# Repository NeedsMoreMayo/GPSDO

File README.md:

# GPSDO
A GPSDO built around readily available hardware

## Current Status
The GPSDO is a work in progress (Jan 2024). It's the first time I'm working with the AVR-Dx family, and it's looking very promissing.
	
## The GPSDO working principle
I've pulled together a number of designs, and ignored a lot of forum comments. The design uses a NEO-M8N GPS as PPS source, the generated pulse is configurable contrary to some sources. The OCXO is a cheap one. I'm using the Time Integration method (TIC) to tune the crystal. The main source of inspiration is the 2011 design by Kasper Kjeld Pedersen (https://n1.taur.dk/gpsdo2a.pdf).

The OCXO clock is fed to the uC as external clock. This way the control runs synchronous to the XO and we need to measure 2 events to keep the OCXO in check:
- the number of pulses contained within 1 sec of PPS. We can count this with the TCD or TCB counter.
- the fraction of the XO pulse that runs out of phase with the PPS. In other words, the out-of-phaseness of the PPS with the rest of the system. We measure this with a TIC (Time Interpolation Counter)

The corrections are fed to a 18-bit DAC which corrects the voltage control of the OCXO. The phase of the XO isn't adjusted, and doesn't need to be. The 1 PPS envelope contains exactly 10M clocks, and the uC is always synced to the clock.

### TIC

### Output stage
The output driver and clock dividers were copied from Bertrand Zauhar's GPSDO design (https://ve2zaz.net/GPS_Std/Downloads/VE2ZAZ_GPS_Derived_Std_QEX_09_10_2006.pdf). The RS422 line driver is changed to DS34C87T because of rise time/propagation delay considerations. Coupling capacitors are High-Voltage devices.

## Parts
- GPS module: GY-GPSV3 NEO-M8N GPS Module from aliexpress.
- OCXO: OC5SC25
- uC: AVR32DB28
- Output line driver: DS34C87T
- LDO: 2 x AZ1117, one for OCXO and one for digital
- DAC: AD5680

## The AVR-DB uC
I originally planned on building it with an atmega. Then changed my mind to an STM32 with ChibiOS. Now I've chosen AVR32DB28. I hope to become familiar enough with it to help porting ChibiOS to the AVR-DX family.

### Compilation
Just type make, the makefile is a template from WinAVR I adapted.
If your avr-gcc doesn't support this device, you probably need to add the support pack from MicroChip's site:
1. goto http://packs.download.atmel.com/
2. download the Atmel AVR-Dx Series Device Support. It's an archive. Uncompress it in ./xyz/
3. copy ./xyz/gcc/dev/avr32db28/avrxmega3/crtavr32db28.o and libavr32db28.a to /yourGCCAVRpath/avr/lib/avrxmega3/
4. copy ./xyz/gcc/dev/avr32db28/device-specs/specs-avr32db28 to /yourGCCAVRpath/avr/lib/avr-gcc/version/gcc/avr/subversion/device-specs/

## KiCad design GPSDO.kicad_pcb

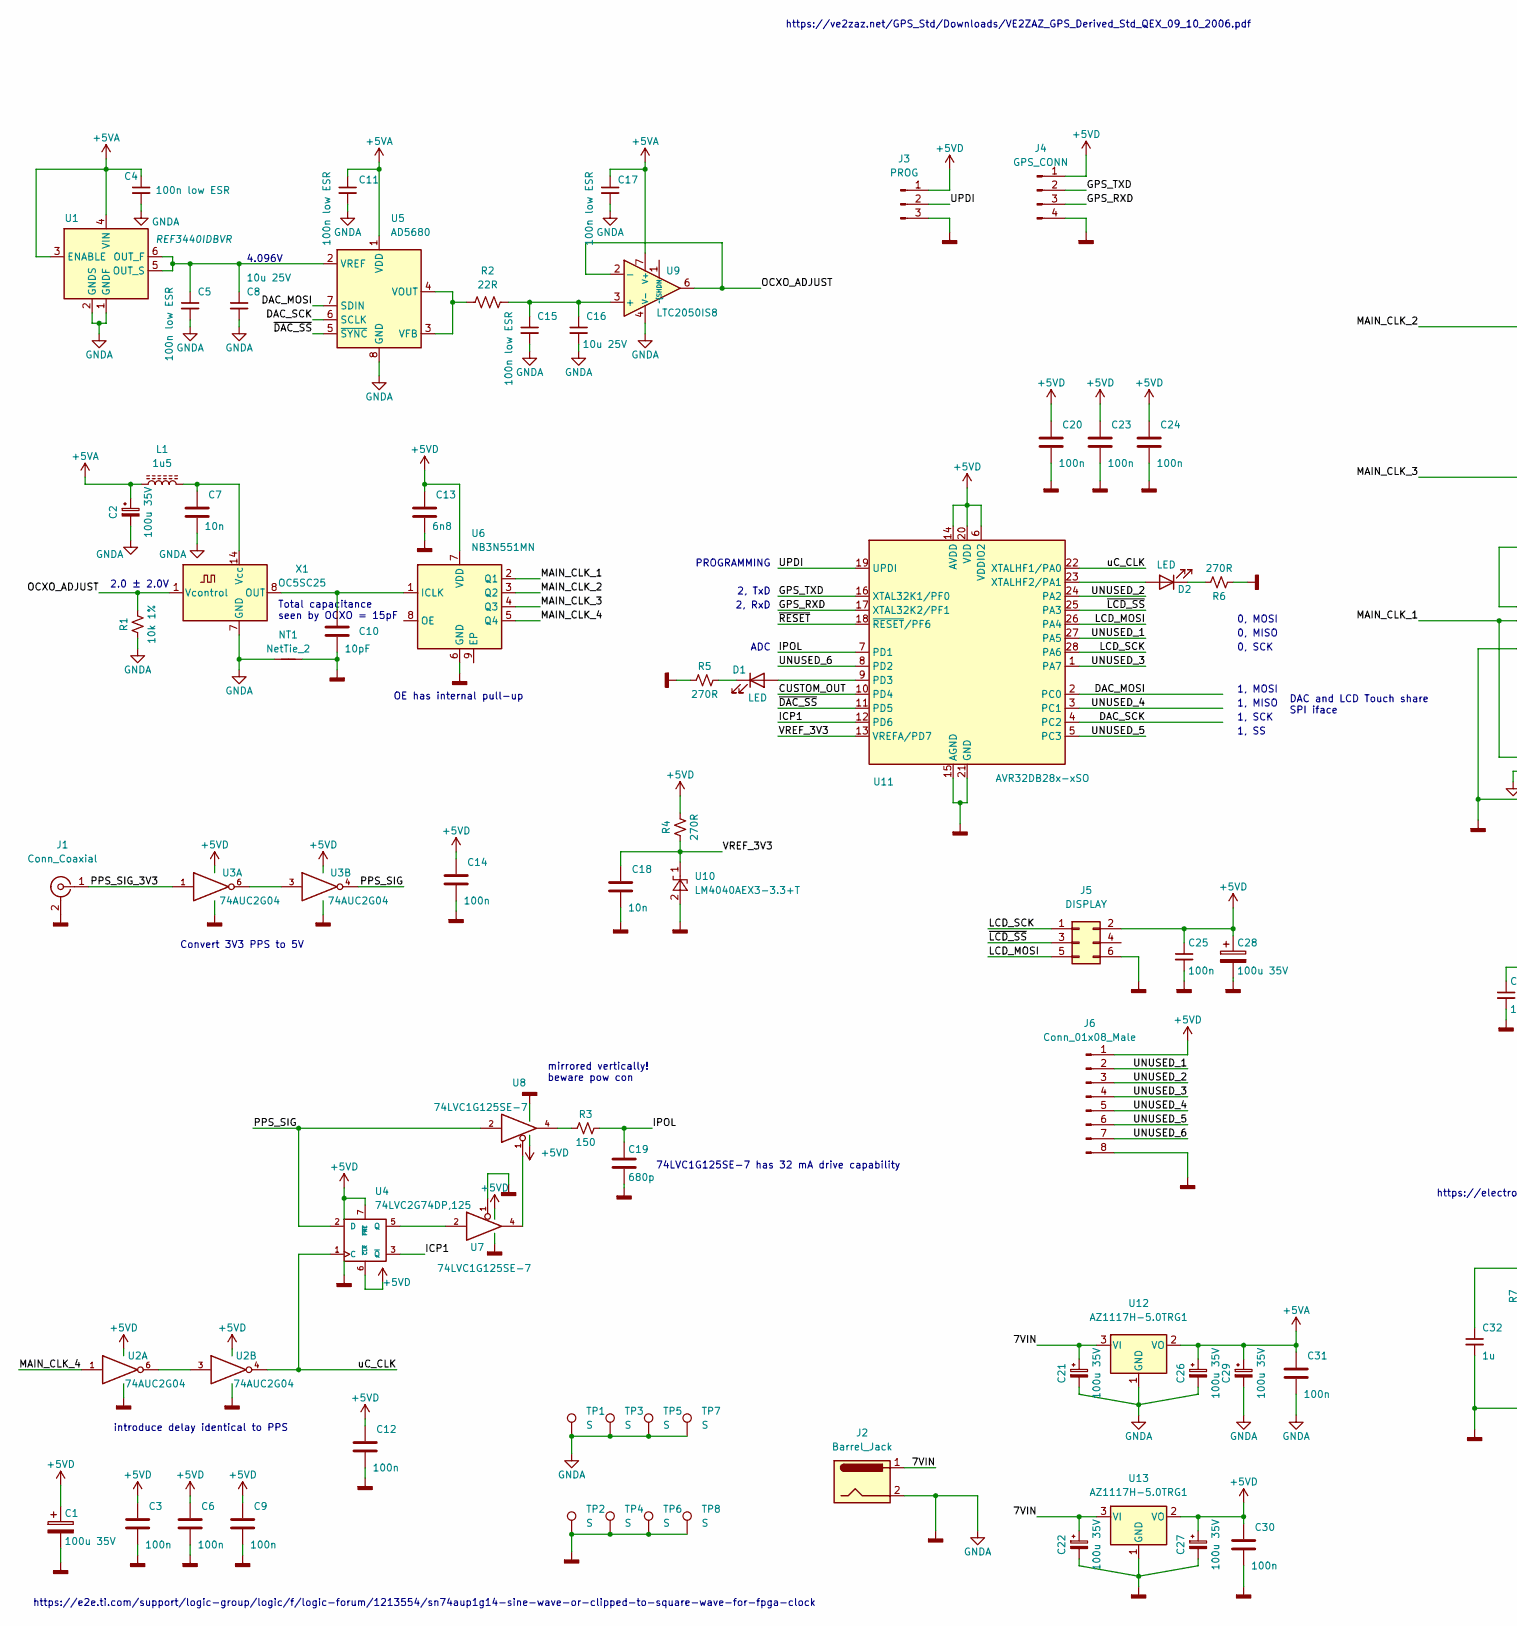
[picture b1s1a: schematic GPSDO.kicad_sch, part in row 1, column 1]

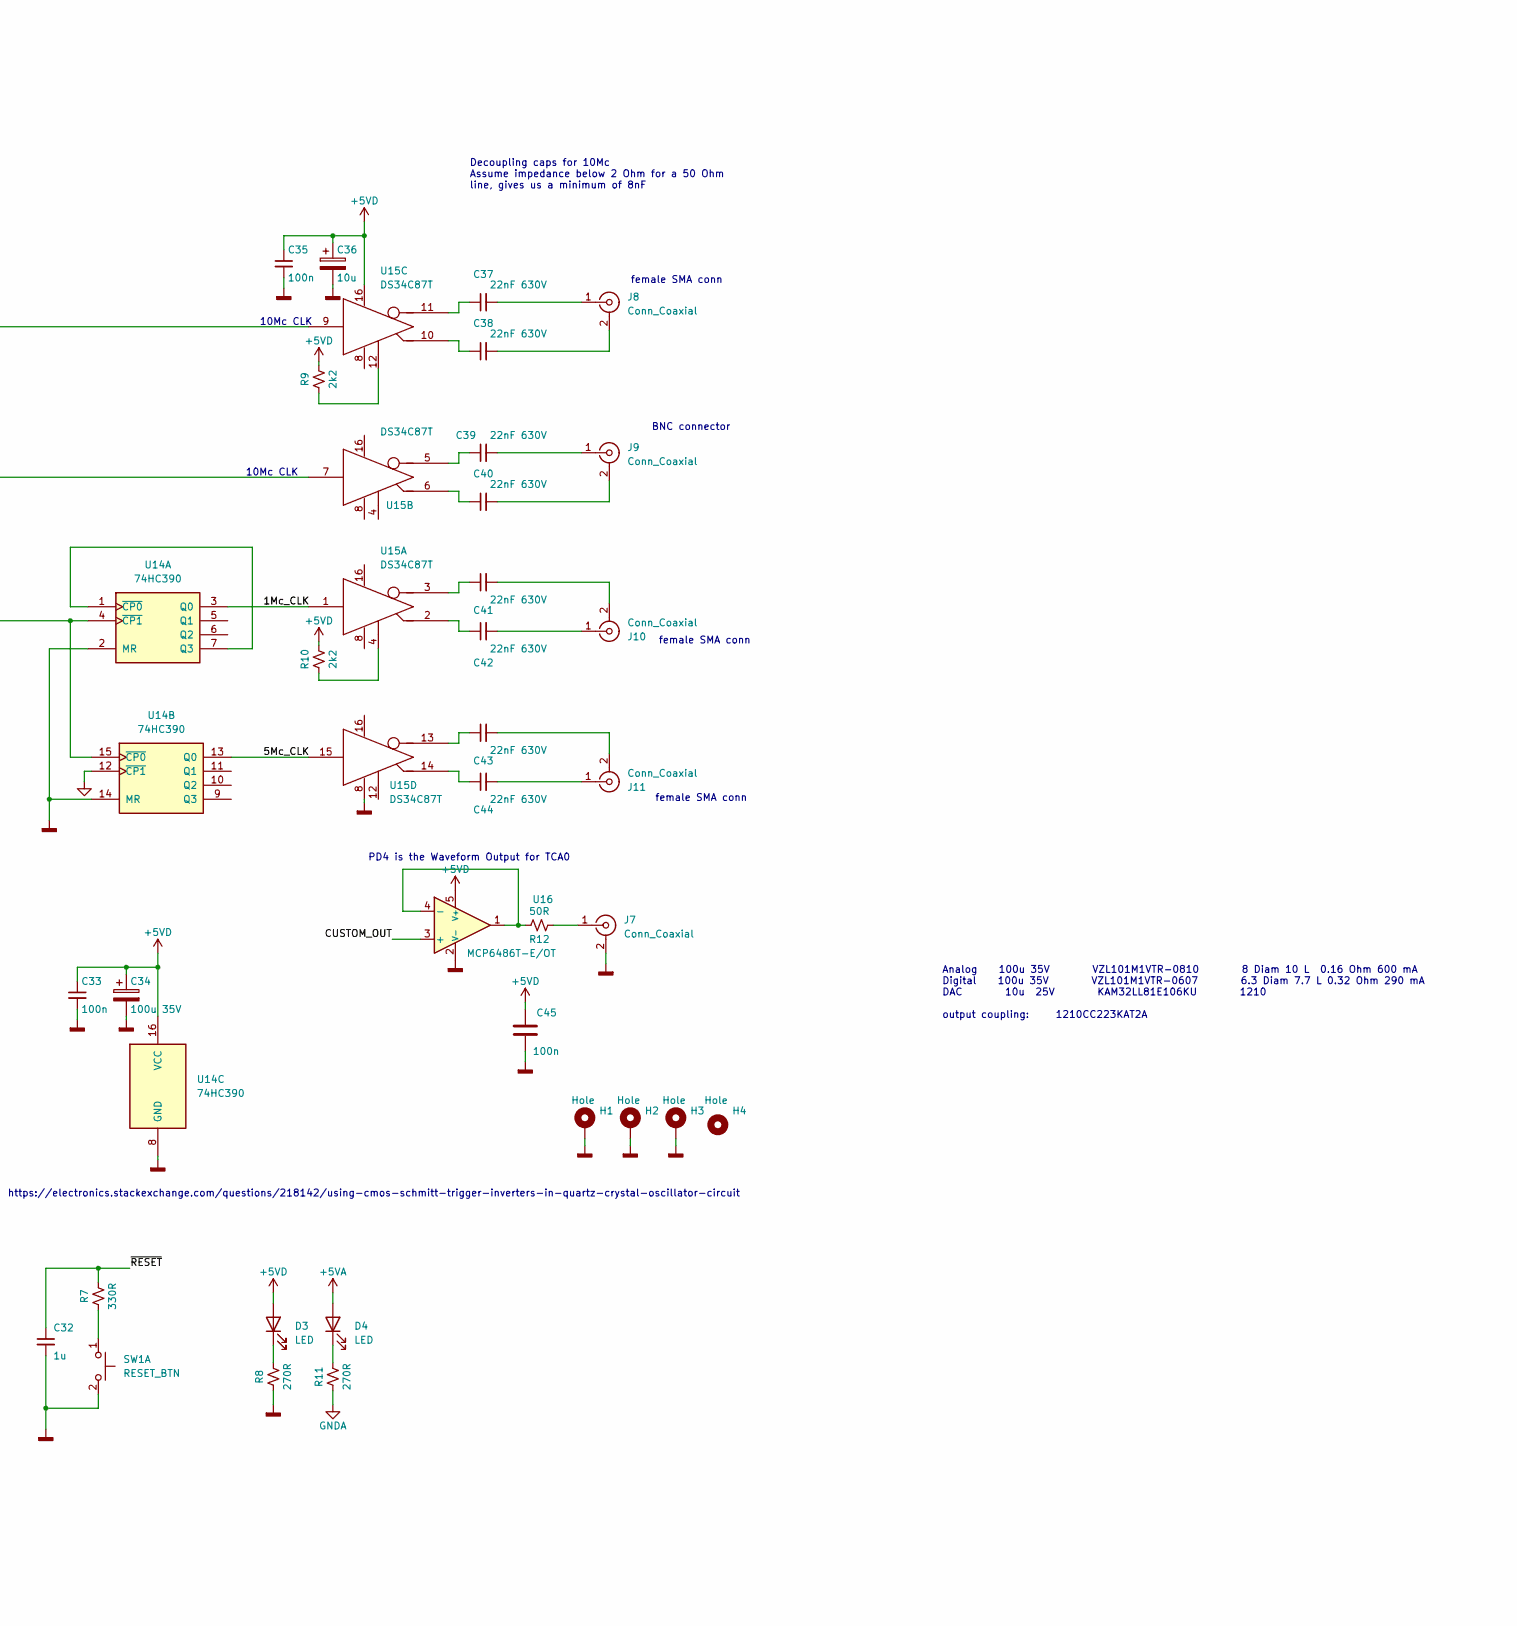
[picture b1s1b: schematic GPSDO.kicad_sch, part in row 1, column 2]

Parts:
C1, C28, C34: 100u 35V; C_Elec_6.3x7.7
C2, C21, C22, C26, C27, C29: 100u 35V; CP_Elec_8x10
C3, C6, C9, C12, C14, C20, C23, C24, C25, C30, C31, C33, C35, C45: 100n; C_0805_2012Metric_Pad1.18x1.45mm_HandSolder
C4, C5, C11, C15, C17: 100n low ESR; C_0805_2012Metric_Pad1.18x1.45mm_HandSolder
C7, C18: 10n; C_0805_2012Metric_Pad1.18x1.45mm_HandSolder
C8, C16: 10u 25V; C_1210_3225Metric_Pad1.33x2.70mm_HandSolder
C10: 10pF; C_0805_2012Metric_Pad1.18x1.45mm_HandSolder
C13: 6n8; C_0805_2012Metric_Pad1.18x1.45mm_HandSolder
C19: 680p; C_0805_2012Metric_Pad1.18x1.45mm_HandSolder
C32: 1u; C_0805_2012Metric_Pad1.18x1.45mm_HandSolder
C36: 10u; C_Elec_4x5.4
C37, C38, C39, C40, C41, C42, C43, C44: 22nF 630V; C_0805_2012Metric_Pad1.18x1.45mm_HandSolder
D1, D2, D3, D4: LED; LED_0805_2012Metric
H1, H2, H3, H4: Hole; MountingHole_3.2mm_M3_Pad_Via
J1: Conn_Coaxial; U.FL_Molex_MCRF_73412-0110_Vertical
J2: Barrel_Jack; BarrelJack_GCT_DCJ200-10-A_Horizontal
J3: PROG; PinHeader_1x03_P2.54mm_Vertical
J4: GPS_CONN; PinHeader_1x04_P2.54mm_Vertical
J5: DISPLAY; PinHeader_2x03_P2.54mm_Vertical
J6: Conn_01x08_Male; PinHeader_2x04_P2.54mm_Vertical
J7, J8, J10, J11: Conn_Coaxial; SMA_Amphenol_901-143_Horizontal
J9: Conn_Coaxial; BNC_TEConnectivity_1478035_Horizontal
L1: 1u5; L_0805_2012Metric
NT1: NetTie_2; SolderJumper-2_P1.3mm_Open_TrianglePad1.0x1.5mm
R1: 10k 1%; R_0805_2012Metric_Pad1.20x1.40mm_HandSolder
R2: 22R; R_0805_2012Metric_Pad1.20x1.40mm_HandSolder
R3: 150; R_0805_2012Metric_Pad1.20x1.40mm_HandSolder
R4, R5, R6, R8, R11: 270R; R_0805_2012Metric_Pad1.20x1.40mm_HandSolder
R7: 330R; R_0805_2012Metric_Pad1.20x1.40mm_HandSolder
R9, R10: 2k2; R_0805_2012Metric_Pad1.20x1.40mm_HandSolder
R12: 50R; R_0805_2012Metric_Pad1.20x1.40mm_HandSolder
SW1: RESET_BTN; BUTTON_5X5
TP1, TP2, TP3, TP4, TP5, TP6, TP7, TP8: S; TestPoint_THTPad_2.0x2.0mm_Drill1.0mm
U1: REF3440IDBVR; SOT-23-6
U2, U3: 74AUC2G04; TSOP-6_1.65x3.05mm_P0.95mm
U4: 74LVC2G74DP,125; TSSOP-8_3x3mm_P0.65mm
U5: AD5680; SOT-23-8_Handsoldering
U6: NB3N551MN; DFN-8-1EP_2x2mm_P0.5mm_EP0.9x1.3mm
U7, U8: 74LVC1G125SE-7; SOT-353_SC-70-5
U9: LTC2050IS8; SO-8_3.9x6.2mm_P1.27mm
U10: LM4040AEX3-3.3+T; SOT-23-3
U11: AVR32DB28x-xSO; SOIC-28W_7.5x17.9mm_P1.27mm
U12, U13: AZ1117H-5.0TRG1; SOT-223-3_TabPin2
U14: 74HC390; SOIC-16_3.9x9.9mm_P1.27mm
U15: DS34C87T; SOIC-16_3.9x9.9mm_P1.27mm
U16: MCP6486T-E/OT; SOT-23-5_HandSoldering
X1: OC5SC25

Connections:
+5VA: C2.1, C4.1, C11.1, C17.1, C26.1, C29.1, C31.2, D4.2 (A), L1.1, U1.3 (ENABLE), U1.4 (VIN), U5.1 (VDD), U9.7 (V+), U12.2 (VO)
+5VD: C1.1, C3.2, C6.2, C9.2, C12.2, C13.2, C14.2, C20.2, C23.2, C24.2, C25.1, C27.1, C28.1, C30.2, C33.1, C34.1, C35.1, C36.1, C45.2, D3.2 (A), J3.1, J4.1, J5.2, J6.1, R4.2, R9.2, R10.2, U2.5 (VCC), U3.5 (VCC), U4.6 (~CLR), U4.7 (~PRE), U4.8 (VCC), U6.7 (VDD), U7.5 (VCC), U8.5 (VCC), U11.6 (VDDIO2), U11.14 (AVDD), U11.20 (VDD), U13.2 (VO), U14.16 (VCC), U15.16 (VCC), U16.5 (V+)
/1Mc_CLK: U14.3 (Q0), U15.1 (INPUT)
/5Mc_CLK: U14.13 (Q0), U15.15 (INPUT)
/7VIN: C21.1, C22.1, J2.1, U12.3 (VI), U13.3 (VI)
/CUSTOM_OUT: U11.10 (PD4), U16.3 (+)
/DAC_MOSI: U5.7 (SDIN), U11.2 (PC0)
/DAC_SCK: U5.6 (SCLK), U11.4 (PC2)
/GPS_RXD: J4.3, U11.17 (XTAL32K2/PF1)
/GPS_TXD: J4.2, U11.16 (XTAL32K1/PF0)
/ICP1: U4.3 (~Q), U11.12 (PD6)
/IPOL: C19.2, R3.1, U11.7 (PD1)
/LCD_MOSI: J5.5, U11.26 (PA4)
/LCD_SCK: J5.1, U11.28 (PA6)
/MAIN_CLK_1: U6.2 (Q1), U14.4 (~CP1), U14.15 (~CP0)
/MAIN_CLK_2: U6.3 (Q2), U15.9 (INPUT)
/MAIN_CLK_3: U6.4 (Q3), U15.7 (INPUT)
/MAIN_CLK_4: U2.1, U6.5 (Q4)
/OCXO_ADJUST: R1.2, U9.2 (-), U9.6, X1.1 (Vcontrol)
/PPS_SIG: U3.4, U4.2 (D), U8.2
/PPS_SIG_3V3: J1.1 (In), U3.1
/UNUSED_1: J6.2, U11.27 (PA5)
/UNUSED_2: J6.3, U11.24 (PA2)
/UNUSED_3: J6.4, U11.1 (PA7)
/UNUSED_4: J6.5, U11.3 (PC1)
/UNUSED_5: J6.6, U11.5 (PC3)
/UNUSED_6: J6.7, U11.8 (PD2)
/UPDI: J3.2, U11.19 (UPDI)
/VREF_3V3: C18.2, R4.1, U10.1 (K), U11.13 (VREFA/PD7)
/uC_CLK: U2.4, U4.1 (C), U11.22 (XTALHF1/PA0)
/~DAC_SS: U5.5 (~SYNC), U11.11 (PD5)
/~LCD_SS: J5.3, U11.25 (PA3)
/~RESET: C32.1, R7.2, U11.18 (~RESET/PF6)
unnamed: D1.2 (A), U11.9 (PD3)
unnamed: D1.1 (K), R5.2
unnamed: D2.2 (A), U11.23 (XTALHF2/PA1)
unnamed: D2.1 (K), R6.2
unnamed: D3.1 (K), R8.2
unnamed: D4.1 (K), R11.2
unnamed: J7.1 (In), R12.1
unnamed: C38.2, J8.2 (Ext)
unnamed: C37.2, J8.1 (In)
unnamed: C40.2, J9.2 (Ext)
unnamed: C39.2, J9.1 (In)
unnamed: C41.2, J10.2 (Ext)
unnamed: C42.2, J10.1 (In)
unnamed: C43.2, J11.2 (Ext)
unnamed: C44.2, J11.1 (In)
unnamed: R3.2, U8.4
unnamed: R7.1, SW1.1 (C)
unnamed: C5.1, C8.1, U1.5 (OUT_S), U1.6 (OUT_F), U5.2 (VREF)
unnamed: U2.3, U2.6
unnamed: U3.3, U3.6
unnamed: U4.5 (Q), U7.2
unnamed: R2.1, U5.3 (VFB), U5.4 (VOUT)
unnamed: C10.2, U6.1 (ICLK), X1.8 (OUT)
unnamed: U7.4, U8.1
unnamed: C15.1, C16.1, R2.2, U9.3 (+)
unnamed: U14.1 (~CP0), U14.7 (Q3)
unnamed: R10.1, U15.4 (ENABLE)
unnamed: C42.1, U15.2 (OUT+)
unnamed: C41.1, U15.3 (OUT-)
unnamed: C40.1, U15.6 (OUT+)
unnamed: C39.1, U15.5 (OUT-)
unnamed: R9.1, U15.12 (ENABLE)
unnamed: C38.1, U15.10 (OUT+)
unnamed: C37.1, U15.11 (OUT-)
unnamed: C44.1, U15.14 (OUT+)
unnamed: C43.1, U15.13 (OUT-)
unnamed: R12.2, U16.1, U16.4 (-)
unnamed: C7.2, L1.2, X1.14 (Vcc)

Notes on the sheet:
10Mc CLK
Analog 100u 35V VZL101M1VTR-0810 8 Diam 10 L 0.16 Ohm 600 mA Digital 100u 35V VZL101M1VTR-0607 6.3 Diam 7.7 L 0.32 Ohm 290 mA DAC 10u 25V KAM32LL81E106KU 1210 output coupling: 1210CC223KAT2A
BNC connector
ADC
1, SS
1, MOSI
Decoupling caps for 10Mc Assume impedance below 2 Ohm for a 50 Ohm line, gives us a minimum of 8nF
0, MOSI
mirrored vertically! beware pow con
DAC and LCD Touch share SPI iface
2, RxD
PROGRAMMING
2.0 ± 2.0V
0, SCK
PD4 is the Waveform Output for TCA0
female SMA conn
1, SCK
4.096V
Total capacitance seen by OCXO = 15pF
introduce delay identical to PPS
0, MISO
1, MISO
OE has internal pull-up
https://electronics.stackexchange.com/questions/218142/using-cmos-schmitt-trigger-inverters-in-quartz-crystal-oscillator-circuit
https://e2e.ti.com/support/logic-group/logic/f/logic-forum/1213554/sn74aup1g14-sine-wave-or-clipped-to-square-wave-for-fpga-clock
https://ve2zaz.net/GPS_Std/Downloads/VE2ZAZ_GPS_Derived_Std_QEX_09_10_2006.pdf
74LVC1G125SE-7 has 32 mA drive capability
2, TxD
Convert 3V3 PPS to 5V

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
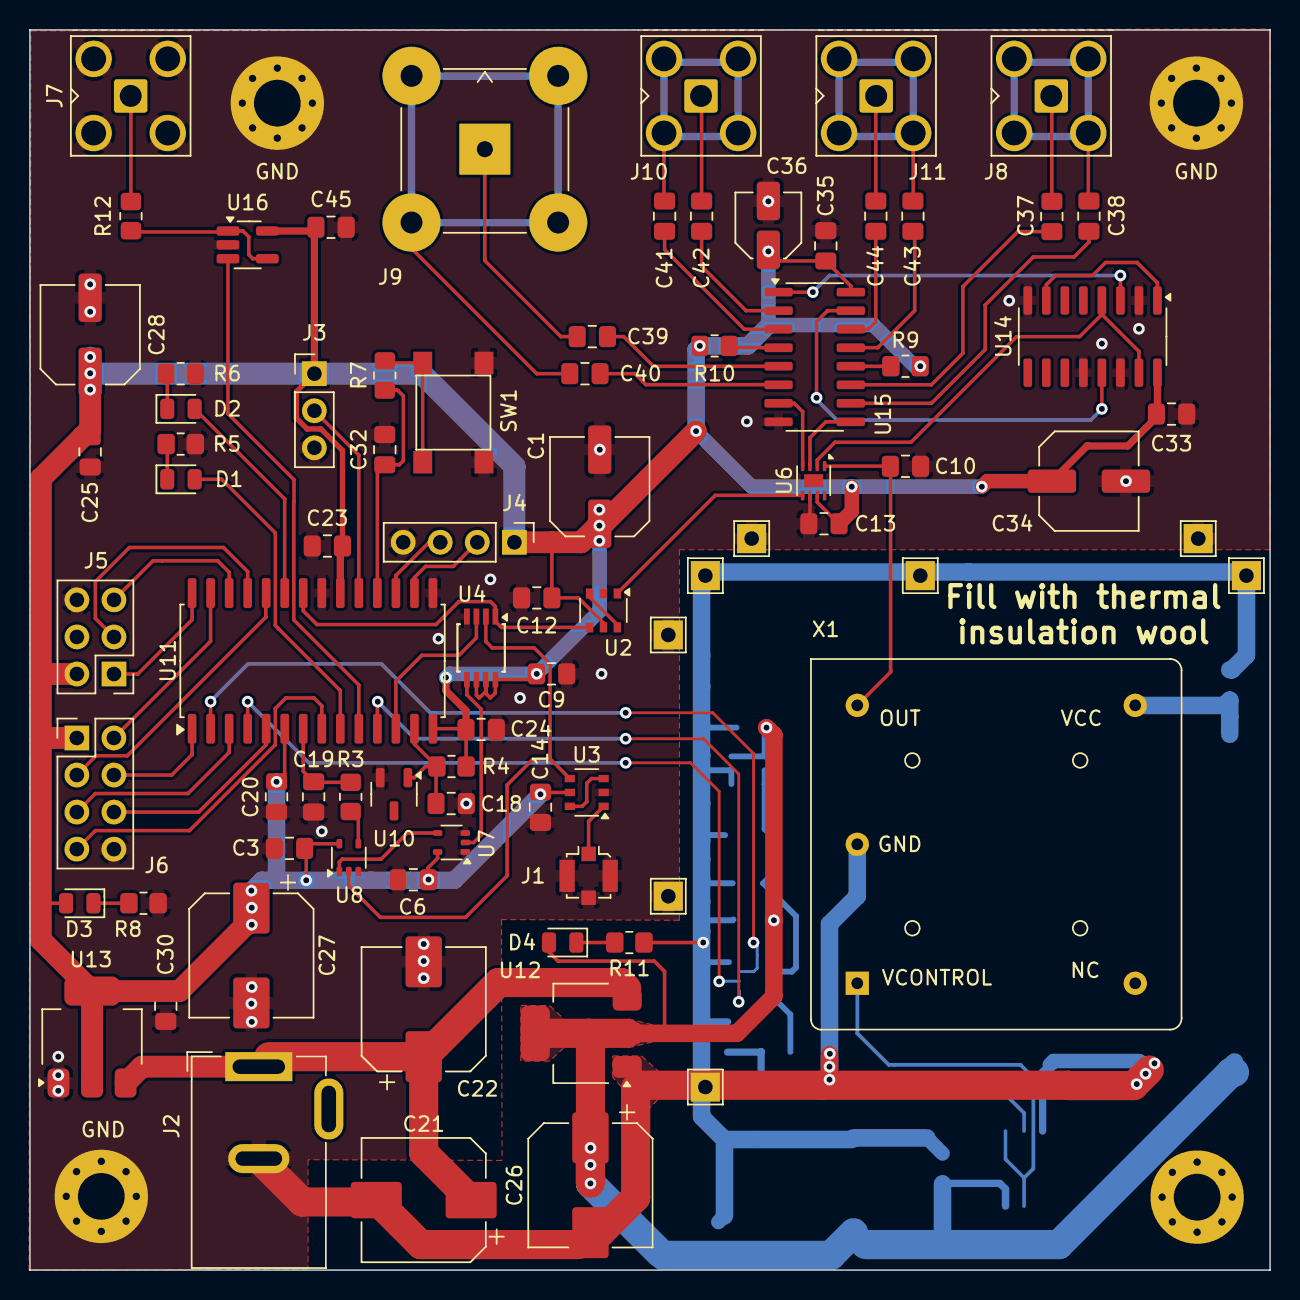
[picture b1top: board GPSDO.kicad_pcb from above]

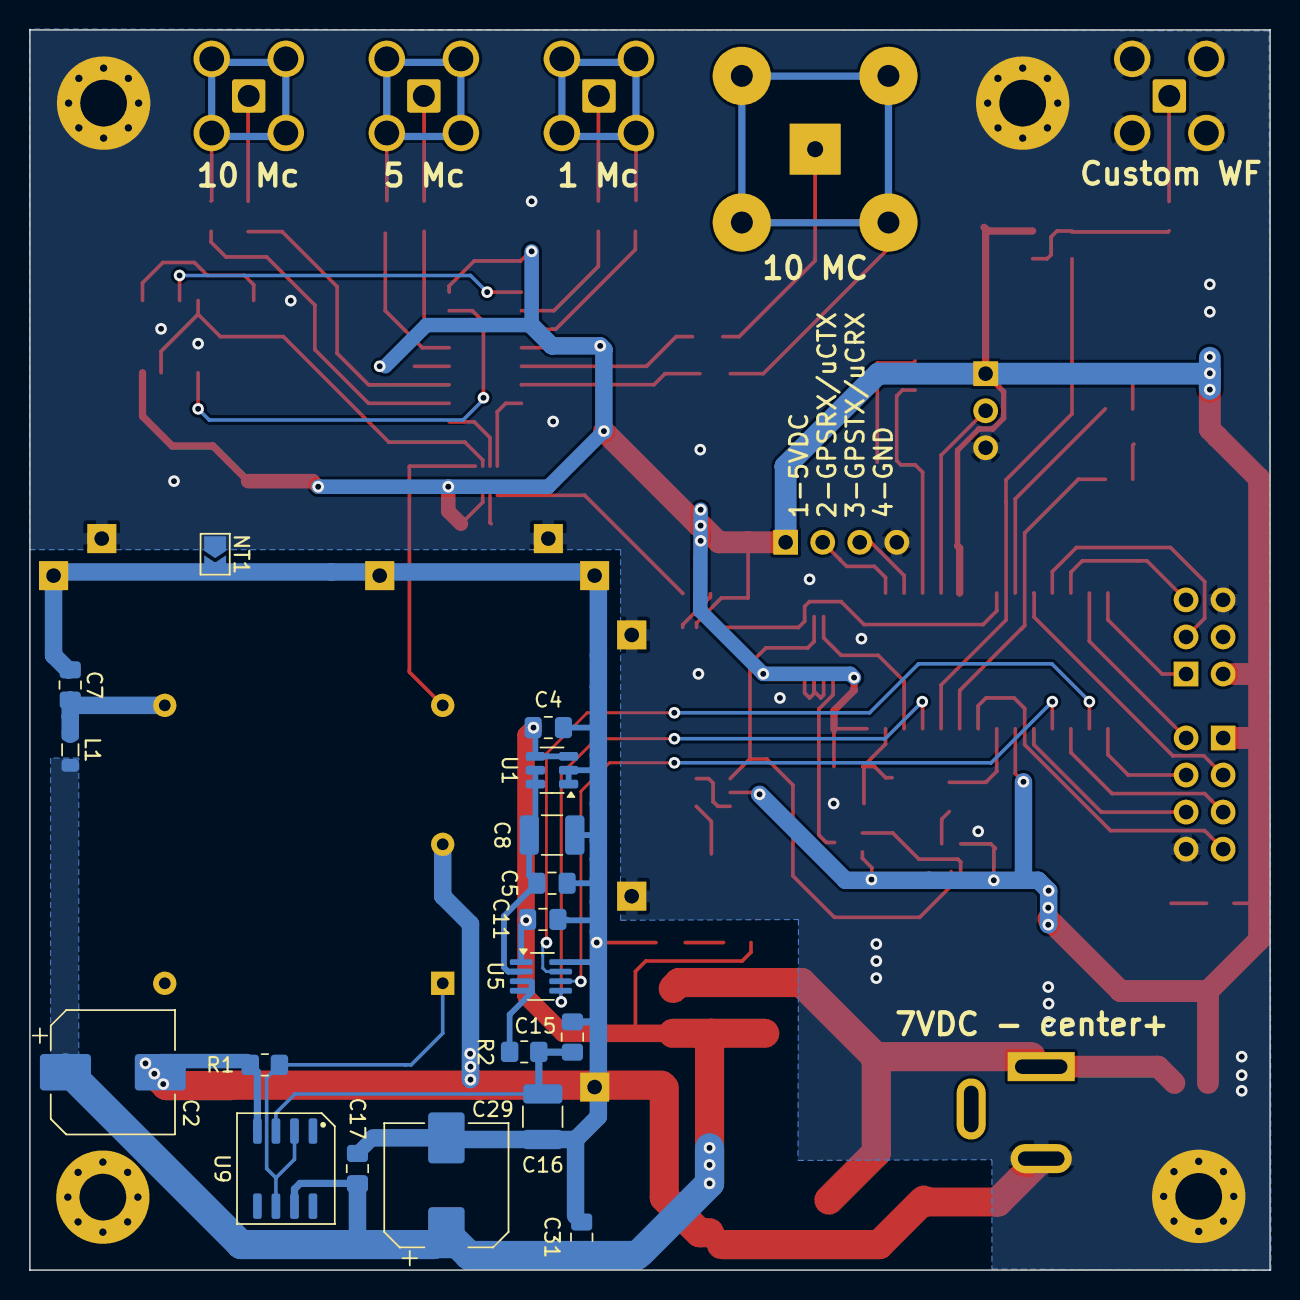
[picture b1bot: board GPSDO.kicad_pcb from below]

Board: 2 copper layers, 85.0 x 85.0 mm, 104 parts (18 on the bottom side), 72 nets.

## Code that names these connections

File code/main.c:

//F_CPU defined in makefile
//#define F_CPU 10000000ul

#include <avr/io.h>
#include <util/delay.h>		//temporary sin
#include <avr/interrupt.h>
//#include <math.h>

#include "uart.h"
#include "adc.h"


//PORT A
#define uC_CLK_PIN		0
#define LCD_SS_PIN		1
#define LCD_RESET_PIN	2
#define LCD_DCRS_PIN	3
#define LCD_MOSI_PIN	4
#define LCD_MISO_PIN	5
#define LCD_SCK_PIN		6
#define TOUCH_SS_PIN	7

//PORT C
#define DAC_MOSI_PIN	0
#define TOUCH_MOSI_PIN	0
#define TOUCH_MISO_PIN	1
#define DAC_SCK_PIN		2
#define TOUCH_SCK_PIN	2
#define TOUCH_IRQ_PIN	3

//PORT D
#define IPOL_PIN		1	//ADC0 AIN1
#define DAC_SS_PIN		2
#define LED_PIN			3
#define CUSTOM_OUT_PIN	4
#define ICP1_PIN		5
#define UNUSED_PIN		6
#define VREF_3V3_PIN	7

//PORT F
#define GPS_TXD_PIN		0
#define GPS_RXD_PIN		1
#define RESET_PIN		6

void PORTS_init(void);
void SPI0_init(void);
void SPI1_init(void);
void DAC_init(void);
void LCD_init(void);
void TOUCH_and_DAC_SPI_init(void);
void TOUCH_IRQ_init(void);
void TOGGLE_LED(void);

extern uint8_t ADC_result_available;

int main(void){
	cli(); //disable interrupts when enabling interrupt handlers
	PORTS_init();
	ADC_init();
	TOUCH_IRQ_init();
	USART2_init();
	sei();//enable interrupts
    while (1){
		TOGGLE_LED();
		_delay_ms(1000);
		if(ADC_result_available){
			//process sample
			
		}
    }
}

ISR(PORTC_PORT_vect){
	if(PORTC_INTFLAGS & (1 << TOUCH_IRQ_PIN)){
		//react
		PORTC.INTFLAGS = 1 << TOUCH_IRQ_PIN;
	}
}


void TOGGLE_LED(){
	PORTD.OUTTGL = 1 << LED_PIN;
}

void TOUCH_IRQ_init(){
	//PORTC pin 3
	//no pull-up, interrupt on rising edge (TODO: check display datasheet)
	PORTC.PIN3CTRL = PORT_ISC_RISING_gc;
}

void PORTS_init(){
	//LCD_SS, LCD_RESET, LCD_DCRS, LCD_MOSI, LCD_SCK and TOUCH_SS are output on PORTA
	PORTA.DIR =   (1 << LCD_SS_PIN)
				| (1 << LCD_RESET_PIN)
				| (1 << LCD_DCRS_PIN)
				| (1 << LCD_MOSI_PIN)
				| (1 << LCD_SCK_PIN)
				| (1 << TOUCH_SS_PIN);
	PORTA.OUT = 0x00;
	
	//DAC_MOSI (TOUCH_MOSI), DAC_SCK (TOUCH_SCK) are output on PORTC
	PORTC.DIR =   (1 << DAC_MOSI_PIN)
				| (1 << DAC_SCK_PIN);
	PORTC.OUT = 0x00;
	
	//LED, DAC_SS and CUSTOM_OUT are output on PORTD
	PORTD.DIR =   (1 << LED_PIN)
				| (1 << DAC_SS_PIN)
				| (1 << CUSTOM_OUT_PIN);
	PORTD.OUT = 0x00;
	
	//GPS_TXD is output on PORTD
	PORTF.DIR = 1 << GPS_TXD_PIN;
	PORTF.OUT = 0x00;
}

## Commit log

2024-01-20 Updated schematic
2024-01-20 Added pulse delay in TIC
2024-01-20 selected TIC components
2024-01-20 Added LEDs, modified SPI
    All SPI uses the same interface now.
    Added extra clocksource to a gpio pin, I don't know whether the internal systick timer will be configurable enough to count ticks
2024-01-20 some pcb placing
    finding optimal location on the pcb
2024-01-21 Update README.md
    Expanded
2024-01-21 Update README.md
    Added Kasper Kjeld Pedersen acknowledgement.
2024-01-21 LCD conn
    Updated LCD & touch connector
2024-01-21 Update .gitignore
    ignore kicad backup files
2024-01-21 Updated output stage and a few bugs
    Different driver, some layout moving
2024-01-21 Update README.md
    Output stage
2024-01-21 Update README.md
    Link to Bertrand Zahaur design
2024-01-21 finalised schematic
    no more big changes
2024-01-21 minor adjustments
2024-01-22 Re-assigned pins
    Preparing for tracing
    Added an UFL output for an arbitrary clock out from the uC. Undecided on PCB dimensions ... will probably change from line driver to RS422 driver and go for a wider PCB
2024-01-23 updated pcb
    more shuffling
2024-01-23 component placement
    inching towards completion
2024-01-24 LDO power supply
    preliminary component choice
2024-01-24 minor update
2024-01-25 intermediate solution for layout
2024-01-25 0CXO chamber complete
2024-01-25 first routing
2024-01-25 DRC & ground planes
2024-01-25 moved components down to accomodate GPS receiver
2024-01-26 GPS module position
    Moved GPS UART connector to 35.1 mm from edge to connect straight to chassis. PCB mounting hole can however not be used.
2024-01-26 Update README.md
    Listed most important component
2024-01-26 makefile & code setup
2024-01-27 Corrected schematic: VREF
    VREF was chosen as 5V instead of 4.096V - corrected with REF3440IDBVR
2024-01-27 TODO: ref/ADC/opamp placement
    The layout for those components is far from optimal
2024-01-27 Flip-flop error
    Wrong device, wasn't 5V tolerant. Corrected
2024-01-27 changed flipflop & added vref
    Flip-flop doesn't really benefit from having a set/reset that can be changed.
    uC benefits from having an external reference. If not placed, internal one can be used.
2024-01-27 updated LCD layout
2024-01-27 updated layout
    Added vref footprint
    Changed pour params for better gnd coverage
    increased digital line distances
2024-01-28 updated code
    added ADC init code
2024-01-28 Re-layout of Vref-OPAMP-DAC
    made analog connections shorter
2024-01-28 added ADC ISR
2024-01-28 Added Touch IRQ handler
    AVR-DX GPIO interrupts get grouped per PORT ... you check them in the ISR. Weird.
2024-01-28 USART2 basic init & handler
2024-01-28 some USART code
    Preliminary, untested
2024-01-29 Added a second LED to GPIO & layout cleanup
2024-01-29 Flipped barrel ground: GND and GNDA, added bottom texts
2024-01-29 ADC and UART code in seperate sources
2024-01-30 Update README.md
    instructions on updating avr-gcc
2024-01-30 Differential pairs leaving the drivers are equal in length
    difference is in the order 0.01 mm
2024-02-01 Final version
    Added custom footprints and symbols (OCXO ...)
2024-02-06 Change of Display
    Changed display interface to one that drives an SPI module (expander) so that a cheap LCD can be used. Then one can put whatever display on it.
2024-02-07 Added vias in the power lines
2024-02-10 Updated 5VA tracks
2024-02-10 5VA and 5VD seperation removed now that layouting finished
2024-02-10 cleaning up pour zones
2024-03-19 Minor aesthetic edits
    Upgraded to Kicad 7.2
    Updated several footprints and changed a few power supply track widths
2024-03-20 Gerbers and final version
